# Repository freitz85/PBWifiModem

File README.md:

**TODO: make this documentation more user friendly and less nerdy**

This repository contains the Hayes Modem & PPP firmware for The Old Net Serial to WIFI Adapter. If you do not care about the source code and just want the firmware, supporting tools and documentation please direct your attention here instead: [https://github.com/TheOldNet/theoldnet-wifi-firmware-binaries](https://github.com/TheOldNet/theoldnet-wifi-firmware-binaries)

The Old Net - RS232 Serial WIFI Modem
=========================

Copyright (C) 2020 Richard Bettridge under GPLv3 license.

based on https://github.com/RolandJuno/esp8266_modem
Copyright (C) 2016 Paul Rickards <rickards@gmail.com> under GPLv3 license.

based on https://github.com/jsalin/esp8266_modem
Copyright (C) 2015 Jussi Salin <salinjus@gmail.com> under GPLv3 license.

## Where to Buy

I make these modems on a custom PCB for a reasonable price. I try to keep the shipping low and the modem always in stock. You can get one at [TheOldNet Store](https://theoldnet.com/store)

## User Manual

Read the docs that ship with the modem here https://github.com/ssshake/vintage-computer-wifi-modem/blob/master/docs/Wifi%20Modem%20Welcome%20Guide.pdf

## Connect To Your Sytem With a Custom Cable

I created this document showing the pin mappings for various systems which do not have a DE/DB9 port. Thanks to members of the community for verifying these pinouts! 

You can reference this to make your own custom cables https://github.com/ssshake/vintage-computer-wifi-modem/blob/master/docs/pin-mapping.md

## To Flash Firmware

To flash the firmware you need three things:

1) This firmware file: https://github.com/ssshake/vintage-computer-wifi-modem/raw/master/firmware/theoldnet_serial_wifi_modem/theoldnet_serial_wifi_modem.ino.nodemcu.bin

2) This program: https://github.com/esphome/esphome-flasher/releases/tag/v1.3.0

3) If on windows, this driver: https://www.silabs.com/documents/public/software/CP210x_Universal_Windows_Driver.zip

Overview
--------
TheOldNet.com is a set of services which aim to revitalize vintage computers by way of providing network access.

The Serial WIFI Modem Emulator is a RS232 DB9 connection which provides a bridge to the internet over WIFI. This device does not show up like a wifi network card on the old device. Rather it shows up as a Hayes compatible dial up modem. Instead of dialing phone numbers to connect to remote computers, it connects to remote computers via telnet. 

This means that you do not need any special software. Any old terminal program works. Instead of dialing a phone number, you "dial" an IP. It's that simple and easy. 

AT command examples
-------------------

* Change baud rate: AT$SB=N (N=300,1200,2400,4800,9600,19200,38400,57600,115200)
* Set WiFi SSID: AT$SSID=YourWiFiSSID
* Set WiFi Password: AT$PASS=YourWiFiPassword
* Connect to WiFi: ATC1
* Save current settigns to NVRAM: AT&W
* Connect by TCP: ATDTsome.bbs.com:23
* Connect by PPP: ATDTPPP or ATDT777 (for systems which cannot dial letters)
* Disable telnet command handling: ATNET0
* Get my IP: ATIP
* Make a HTTP GET request: ATGEThttp://host:80/path
* Answer a RING: ATA
* Disconnect: +++ (following a delay of a second)
* Speed Dial: ATDSN (N=0-9)
* Set Speed Dial: AT&ZN=HOST:PORT (N=0-9)
* Complete commands can be found with AT? or ATHELP

Note that the key and port are optional parameters. Port defaults to 23. All parameters are case sensitive, the command itself not. You must always connect to an access point before dialing, otherwise you get an error. When you connect to WIFI you get either OK or ERROR after a while, depending on if it succeeded. If you get ERROR the connection might still occur by itself some time later, in case you had a slow AP or slow DHCP server in the network. When dialing, you get either CONNECT when successfully connected or ERROR if the connection couldn't be made. Reasons can be that the remote service is down or the host name is mistyped.

Default Baud rate is defined in the code as 300. 2400 is safe for C64 and 19200 for any PC and Amiga. 115200 for PC's with "new" 16550 UART.  You must always have that default rate on the terminal when powering on. After giving a command for a higher rate nothing is replied, just switch to the new baud rate in your terminal as well. Then you can give next command in the new baud rate. Note that the first command after switching baud rate might fail because the serial port hardware is not fully synchronized yet, so it might be good idea to simply give "AT" command and wait for "ERROR" or "OK" before giving an actual command.

You can always default the baud rate back to 300 baud by pressing and holding the button (GPIO 0 to ground) for 5 seconds until the LED (GPIO 5) flashes fast.

Example communication
---------------------
    
    OK
    at$ssid=MyWiFiNetwork
    
    OK
    at$pass=MyPassword
    
    OK
    atc1
    
    CONNECTING TO SSID MyWiFiNetwork......
    CONNECTED TO MyWiFiNetwork
    IP ADDRESS: 192.168.2.3
    
    OK
    atdtbat.org:23
    DIALING bat.org:23
    
    CONNECT 2400

               ^_                                   _^
              /  \__________   /\___/\   __________/  \
             /              \  \     /  /              \
            /      \   \     \_/ ` ' \_/     /   /      \
           /   _/\  \   \        ---        /   /  /\_   \      Logo by:
          /  _/   \  \   \                 /   /  /   \_  \        Saruman
         / _/      \          _       _          /      \_ \
        /_/         \/\/\/\/\/ \_____/ \/\/\/\/\/         \_\
       //                                                   \\
    .       Welcome to BatMUD, Online since 14th April 1990!
    .     EMail: batry@bat.org about problems concerning BatMUD
    
         This machine is owned by B.A.T. ry, a non-profit organization, 
                        and is hosted at Nebula, Finland.

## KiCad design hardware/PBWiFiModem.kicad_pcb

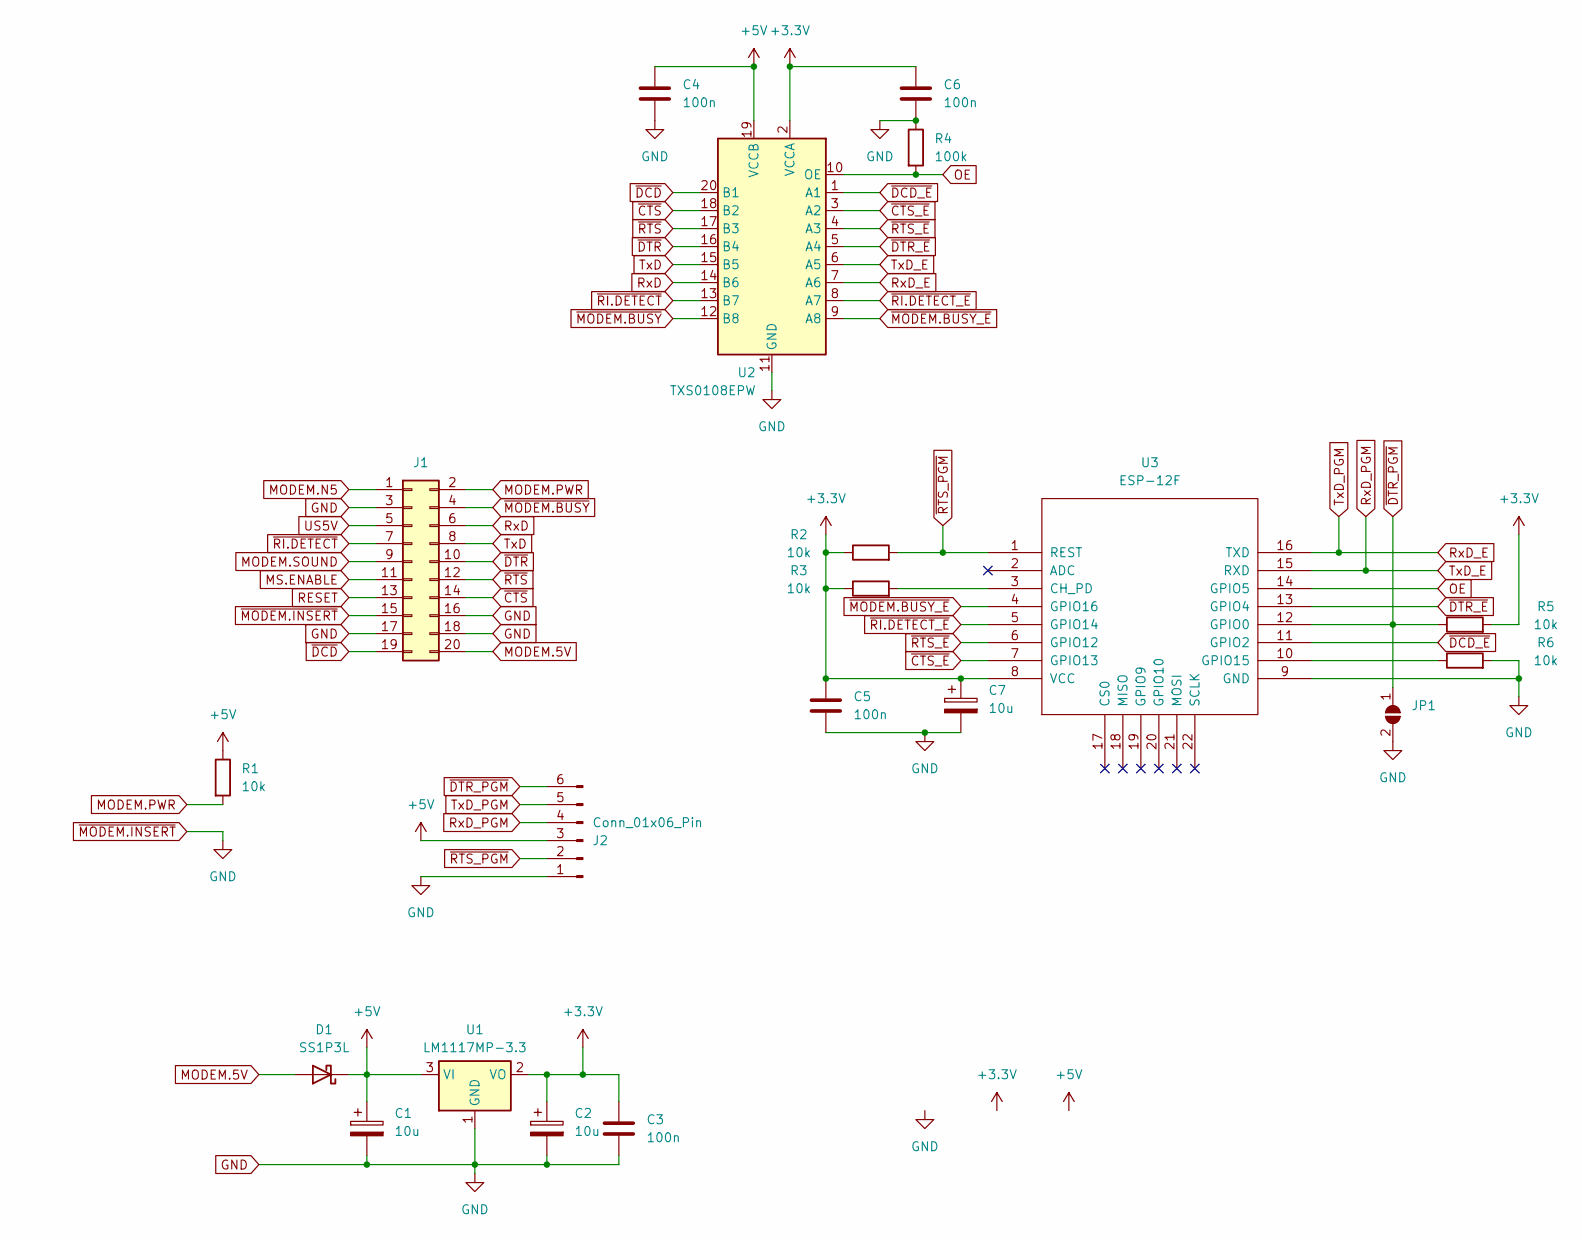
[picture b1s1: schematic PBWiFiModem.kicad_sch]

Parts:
C1, C2, C7: 10u; C_1206_3216Metric
C3, C4, C5, C6: 100n; D_0805_2012Metric
D1: SS1P3L; D_MicroSMP_AK
J1: Conn_02x10_Odd_Even; PinSocket_2x10_P1.27mm_Vertical_SMD
J2: Conn_01x06_Pin; PinHeader_1x06_P2.54mm_Horizontal
JP1: SolderJumper_2_Open; SolderJumper-2_P1.3mm_Open_RoundedPad1.0x1.5mm
R1, R2, R3, R5, R6: 10k; R_0805_2012Metric
R4: 100k; R_0805_2012Metric
U1: LM1117MP-3.3; SOT-223-3_TabPin2
U2: TXS0108EPW; TSSOP-20_4.4x6.5mm_P0.65mm
U3: ESP-12F; ESP-12E

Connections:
+3.3V: C2.1, C3.1, C5.1, C6.1, C7.1, R2.1, R3.1, R5.2, U1.2 (VO), U2.2 (VCCA), U3.8 (VCC)
+5V: C1.1, C4.1, D1.1 (K), J2.3, R1.1, U1.3 (VI), U2.19 (VCCB)
GND: C1.2, C2.2, C3.2, C4.2, C5.2, C6.2, C7.2, J1.3, J1.15, J1.16, J1.17, J1.18, J2.1, JP1.2 (B), R4.1, R6.2, U1.1 (GND), U2.11 (GND), U3.9 (GND)
MODEM.5V: D1.2 (A), J1.20
MODEM.N5: J1.1
MODEM.PWR: J1.2, R1.2
MODEM.SOUND: J1.9
MS.ENABLE: J1.11
unnamed: R3.2, U3.3 (CH_PD)
unnamed: R6.1, U3.10 (GPIO15)
OE: R4.2, U2.10 (OE), U3.14 (GPIO5)
RESET: J1.13
RxD: J1.6, U2.14 (B6)
RxD_E: J2.5, U2.7 (A6), U3.16 (TXD)
RxD_PGM: J2.4, U2.6 (A5), U3.15 (RXD)
TxD: J1.8, U2.15 (B5)
US5V: J1.5
~CTS_E: U2.3 (A2), U3.7 (GPIO13)
~CTS: J1.14, U2.18 (B2)
~DCD_E: U2.1 (A1), U3.11 (GPIO2)
~DCD: J1.19, U2.20 (B1)
~DTR_E: U2.5 (A4), U3.13 (GPIO4)
~DTR_PGM: J2.6, JP1.1 (A), R5.1, U3.12 (GPIO0)
~DTR: J1.10, U2.16 (B4)
~MODEM.BUSY_E: U2.9 (A8), U3.4 (GPIO16)
~MODEM.BUSY: J1.4, U2.12 (B8)
~RI.DETECT_E: U2.8 (A7), U3.5 (GPIO14)
~RI.DETECT: J1.7, U2.13 (B7)
~RTS_E: U2.4 (A3), U3.6 (GPIO12)
~RTS_PGM: J2.2, R2.2, U3.1 (REST)
~RTS: J1.12, U2.17 (B3)

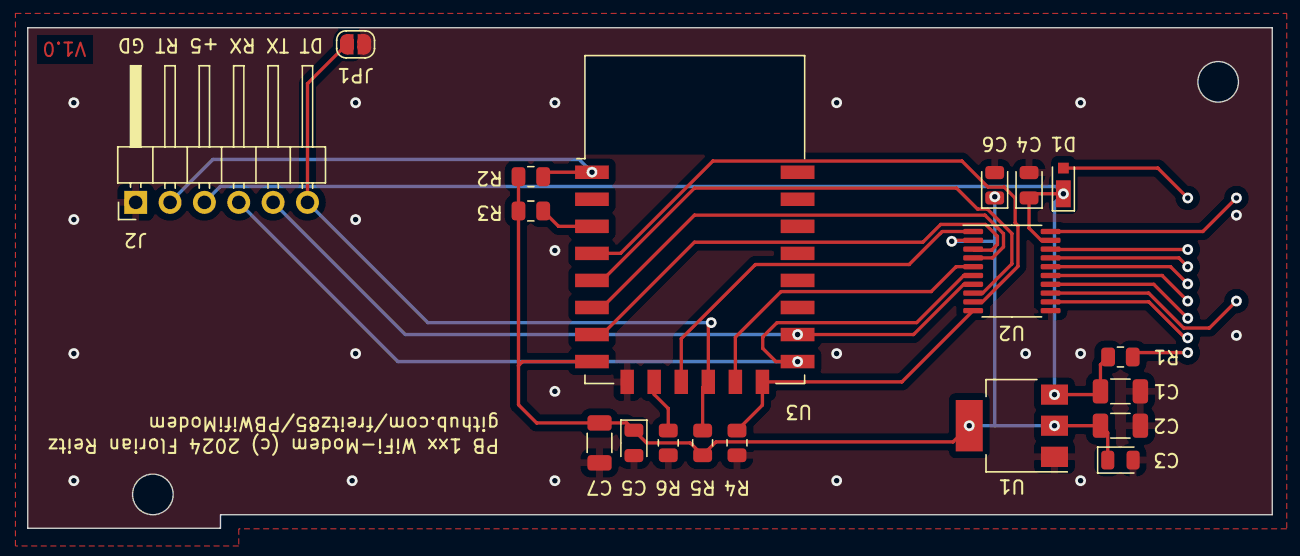
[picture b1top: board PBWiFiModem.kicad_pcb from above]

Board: 2 copper layers, 92.0 x 37.0 mm, 20 parts (1 on the bottom side), 26 nets.

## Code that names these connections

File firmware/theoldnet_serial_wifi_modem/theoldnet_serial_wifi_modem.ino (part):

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#define BUSY_MSG_LEN    80
#define LAST_ADDRESS    780

#define FLASH_BUTTON 0       // GPIO0 (programmind mode pin)
#define LED_PIN 16          // Status LED
#define LED_ESP_PIN 2
#define DCD_PIN 2          // DCD Carrier Status
//#define RTS_PIN 4         // RTS Request to Send, connect to host's CTS pin
//#define CTS_PIN 5         // CTS Clear to Send, connect to host's RTS pin


//Then when a DTE (such as a computer) wants to stop the data sending into it, it sets RTS to LOW. 
//The low state of the RTS (Request To Send) signal equal to -12V means "Do not send to me" (stop sending). 
//When the computer is ready to receive some bytes it sets RTS to HIGH (+12V) and the flow of bytes to it resumes. 
//Flow control signals are always sent in a direction opposite to the flow of bytes that is being controlled. 
//DCE equipment (modems) works the same way but sends the stop signal out the CTS pin. 
//If you don't need the flow control then you may not connect corresponding pins. In the most simple case you may connect 3 pins only.

//https://www.best-microcontroller-projects.com/how-rs232-works.html#handshake
//Looks like for bidirectional flow control DTR and DSR will be required. 
//!!! PIN 13 is labelled as CTS on the PCB and 15 as RTS. I believe these are backwards now by looking at a DTE to DCS straight through diagram
//I believe the hardware traces are correct:
//RTS 13 -> R2OUT -> R2IN -> DB9 PIN 7
//CTS 15 -> T2IN -> T2OUT -> DB9 PIN 8
//RTS IS INBOUND FROM PC
//CTS IS OUTBOUND FROM PC
#define RTS_PIN 13         // RTS Request to Send, connect to host's CTS pin RTS is DB9 PIN 7
#define CTS_PIN 15         // CTS Clear to Send, connect to host's RTS pin CTS is DB9 PIN 8

// Global variables
String build = "01102023";
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
void setCarrierDCDPin(byte carrier) {
  if (pinPolarity == P_NORMAL) carrier = !carrier;
  digitalWrite(DCD_PIN, carrier);
}

void waitForSpace() {
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  if (flowControl == F_NONE) return;
  //disabled in case it's accidentally pausing
//  if (flowControl == F_HARDWARE) {
//    if (digitalRead(CTS_PIN) == pinPolarity) txPaused = true;
//    else txPaused = false;
//  }
  if (flowControl == F_SOFTWARE) {
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
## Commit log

2021-01-29 updated folder structure and produced a new firmware binary
2021-03-01 added modem photo
2021-09-16 updated docs
2021-09-16 sinclair pinmapping
2021-09-16 rename file
2021-09-17 pinmapping
2021-09-17 update pdf
2021-09-17 update docs
2021-09-22 Fix baud selection issue
2021-09-22 Fix spacing
2022-03-11 add support for gopher protocol
2022-03-21 initial PPP support. It links up but doesn't pass any traffic
2022-03-23 it actually works! Disabled some debug output
2022-03-24 PPP code cleanups and fix an off-by-one in DNS server offering
2022-03-29 show PPP status on web page and ATI command
2022-03-29 mention PPP in the top level README.md
2022-04-06 new binary
2022-04-10 PPP: offer DNS server
2022-04-19 PPP error handling was completely wrong
2022-06-03 Add numeric value for fake PPP host
2022-06-27 double led
2022-07-08 update image for docs
2023-01-09 disables flow control stuff, adds ota updates
2023-01-09 ota firmware!
2023-01-10 compares firmware version to latest and notifies user
2023-01-10 cleaned up firmware check
2023-01-10 mega refactor
2023-01-10 more read by refactor
2023-01-10 mega refactor round 2?
2023-01-10 Release 01102023: What a great day
2023-01-10 more code clean up
2023-01-11 new webserver
2023-01-11 status complete, added modem sound
2023-01-11 confirm before doing something destructive
2023-01-11 shows saved settings
2024-11-25 Hardware added
2024-11-27 Connector changed to SMD

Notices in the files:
firmware/theoldnet_serial_wifi_modem/theoldnet_serial_wifi_modem.ino:
Copyright (C) 2020 Richard Bettridge (@theoldnet)
This program is free software: you can redistribute it and/or modify
it under the terms of the GNU General Public License as published by
the Free Software Foundation, either version 3 of the License, or
(at your option) any later version.
hardware/PBWiFiModem.kicad_pcb:
PB 1xx WiFi-Modem (c) 2024 Florian Reitz
